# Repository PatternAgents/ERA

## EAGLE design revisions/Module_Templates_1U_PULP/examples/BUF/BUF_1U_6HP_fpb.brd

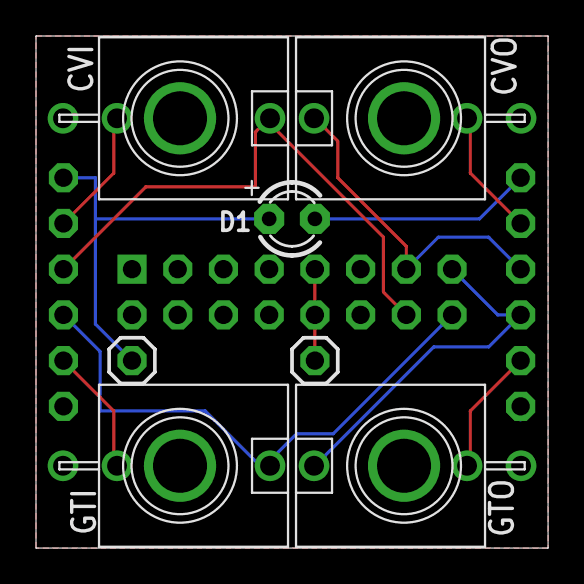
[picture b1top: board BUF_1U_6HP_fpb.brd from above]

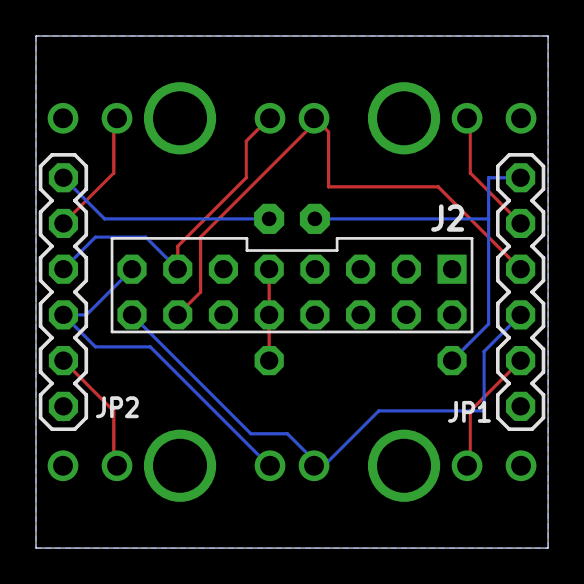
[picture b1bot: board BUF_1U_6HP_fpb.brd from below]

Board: 2 copper layers, 28.4 x 28.4 mm, 11 parts (3 on the bottom side), 12 nets.

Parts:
CVI: JACK-3_5MM-MONO-SW-WQP_PJ302-12; WQP_PJ301M-12
CVO: JACK-3_5MM-MONO-SW-WQP_PJ302-12; WQP_PJ301M-12
D1: LED; LED3MM
GTI: JACK-3_5MM-MONO-SW-WQP_PJ302-12; WQP_PJ301M-12
GTO: JACK-3_5MM-MONO-SW-WQP_PJ302-12; WQP_PJ301M-12
J2: ERA-NOSILK
J12, J13: 1X01
JP1, JP2: 1X06
TOMMOXON: BY_CC_SA_TEXTNULL; NULL_SYM

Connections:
CVI: CVI.TIP, J2.14, JP1.4
CVI_NOR: CVI.TIP_SW, JP1.5
CVO: CVO.TIP, J2.13, JP2.4
CVO_NOR: CVO.TIP_SW, JP2.5
GND: CVI.SLEEVE, CVO.SLEEVE, GTI.SLEEVE, GTO.SLEEVE, J2.3, J2.4, J2.5, J2.6, JP1.1, JP2.1
GTI: GTI.TIP, J2.16, JP1.3
GTI_NOR: GTI.TIP_SW, JP1.2
GTO: GTO.TIP, J2.15, JP2.3
GTO_NOR: GTO.TIP_SW, JP2.2
LED_A: D1.A, J13.1, JP1.6
LED_K: D1.K, JP2.6
unnamed: J2.9, J2.10, J12.1

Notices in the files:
parts and their libraries:
PatternAgents-Logos: License : http://creativecommons.org/licenses/by-sa/3.0
(Creative Commons 3.0)
PatternAgents-ProtoPads: License : http://creativecommons.org/licenses/by-sa/4.0
(Creative Commons 4.0)
